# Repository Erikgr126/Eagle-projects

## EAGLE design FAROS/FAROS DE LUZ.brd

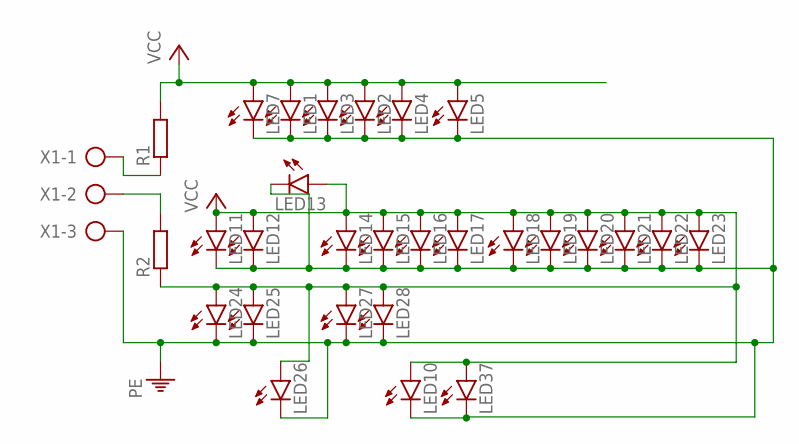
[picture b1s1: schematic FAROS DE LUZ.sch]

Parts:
LED1, LED2, LED3, LED4, LED5, LED7: LED10MM
LED10, LED11, LED12, LED13, LED14, LED15, LED16, LED17, LED18, LED19, LED20, LED21, LED22, LED23, LED24, LED25, LED26, LED27, LED28, LED37: LED5MM
R1, R2: R-EU_0204/7; 0204/7
X1: AK500/3-H

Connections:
unnamed: R1.1, X1.1
unnamed: R2.2, X1.2
PE: LED1.K (C), LED2.K (C), LED3.K (C), LED4.K (C), LED5.K (C), LED7.K (C), LED10.K (C), LED11.K (C), LED12.K (C), LED13.K (C), LED14.K (C), LED15.K (C), LED16.K (C), LED17.K (C), LED18.K (C), LED19.K (C), LED20.K (C), LED21.K (C), LED22.K (C), LED23.K (C), LED24.K (C), LED25.K (C), LED26.K (C), LED27.K (C), LED28.K (C), LED37.K (C), X1.3
VCC: LED1.A, LED2.A, LED3.A, LED4.A, LED5.A, LED7.A, LED10.A, LED11.A, LED12.A, LED13.A, LED14.A, LED15.A, LED16.A, LED17.A, LED18.A, LED19.A, LED20.A, LED21.A, LED22.A, LED23.A, LED24.A, LED25.A, LED26.A, LED27.A, LED28.A, LED37.A, R1.2, R2.1

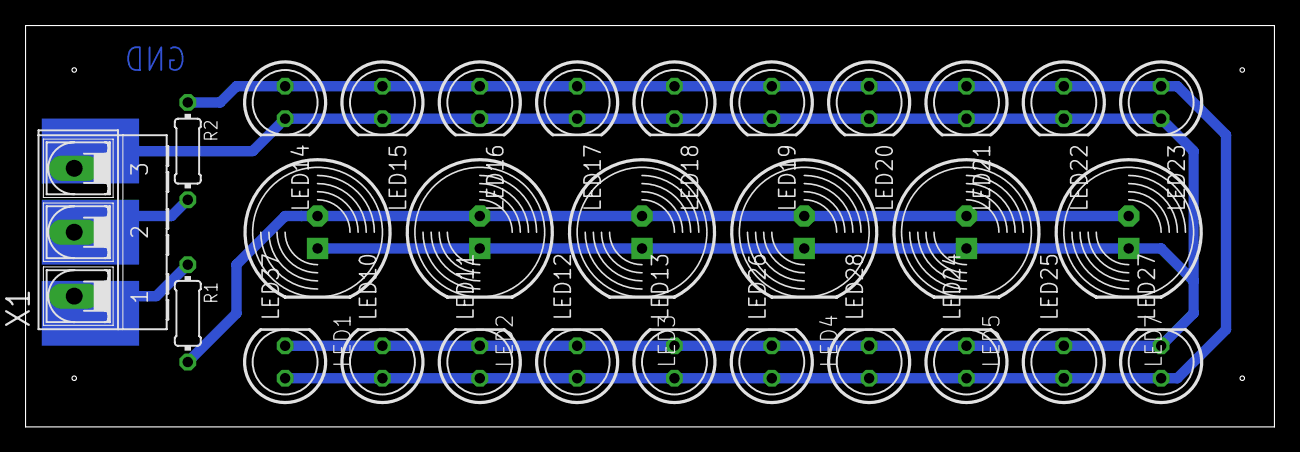
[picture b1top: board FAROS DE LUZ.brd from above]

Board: 2 copper layers, 97.8 x 31.4 mm, 29 parts (0 on the bottom side), 4 nets.

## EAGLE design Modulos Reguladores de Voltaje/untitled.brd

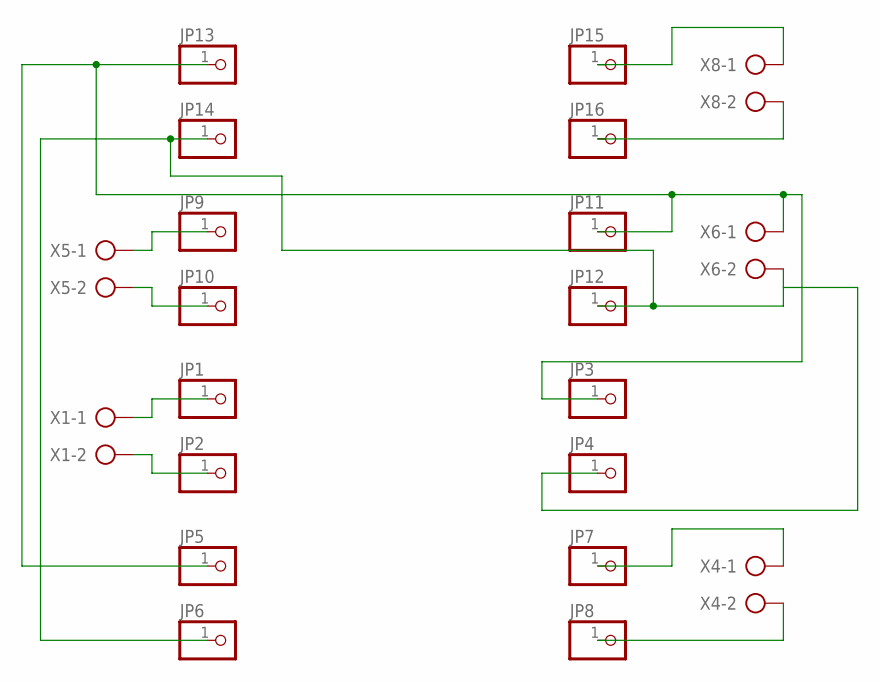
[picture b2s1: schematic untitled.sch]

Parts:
JP1, JP2, JP3, JP4, JP5, JP6, JP7, JP8, JP9, JP10, JP11, JP12, JP13, JP14, JP15, JP16: PINHD-1X1; 1X01
X1, X4, X5, X6, X8: AK500/2-H

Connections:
unnamed: JP1.1, X1.1
unnamed: JP2.1, X1.2
unnamed: JP3.1, JP5.1, JP11.1, JP13.1, X6.1
unnamed: JP4.1, JP6.1, JP12.1, JP14.1, X6.2
unnamed: JP7.1, X4.1
unnamed: JP8.1, X4.2
unnamed: JP9.1, X5.1
unnamed: JP10.1, X5.2
unnamed: JP15.1, X8.1
unnamed: JP16.1, X8.2

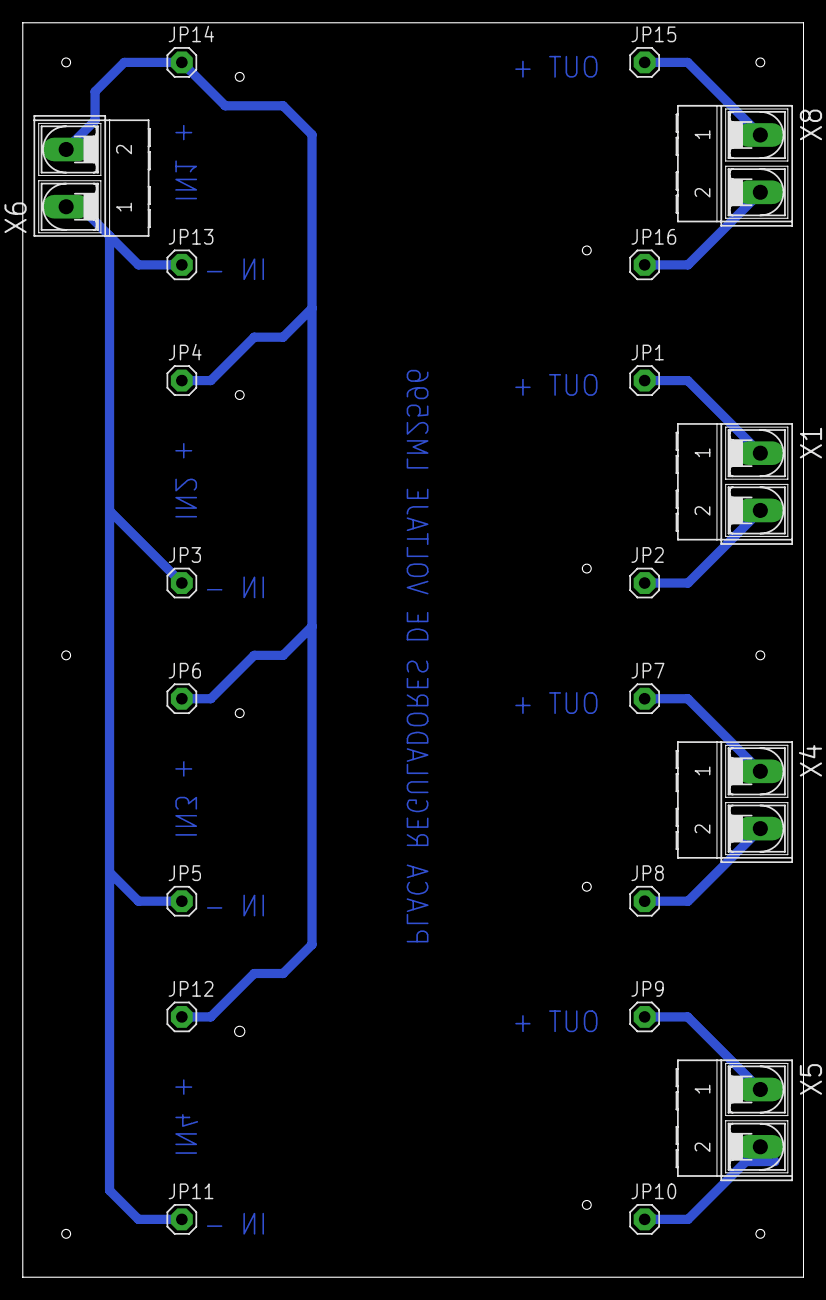
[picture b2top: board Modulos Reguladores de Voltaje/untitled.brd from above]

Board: 2 copper layers, 68.6 x 110.2 mm, 21 parts (0 on the bottom side), 10 nets.

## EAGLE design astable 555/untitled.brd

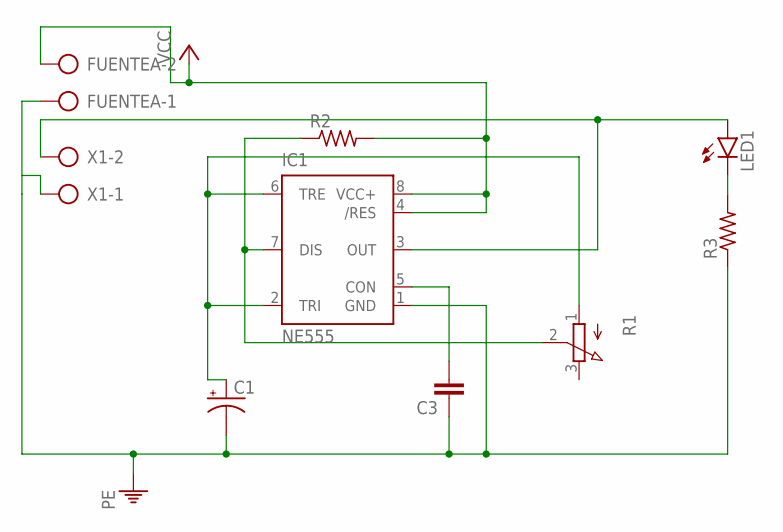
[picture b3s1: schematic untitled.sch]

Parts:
C1: CPOL-USE1.8-4; E1,8-4
C3: C2,5-3; C2.5-3
FUENTEA: AK500/2-H
IC1: NE555; DIL-08
LED1: LED5MM
R1: 3RP/1610N
R2, R3: R-US_0204/7; 0204/7
X1: AK500/2-H

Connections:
unnamed: IC1.3 (OUT), LED1.A, X1.2
unnamed: C1.+, IC1.2 (TRI), IC1.6 (TRE), R1.1 (A)
unnamed: LED1.K (C), R3.2
unnamed: C3.2, IC1.5 (CON)
unnamed: IC1.7 (DIS), R1.2 (S), R2.1
PE: C1.-, C3.1, FUENTEA.1, IC1.1 (GND), R3.1, X1.1
VCC: FUENTEA.2, IC1.4 (/RES), IC1.8 (VCC+), R2.2

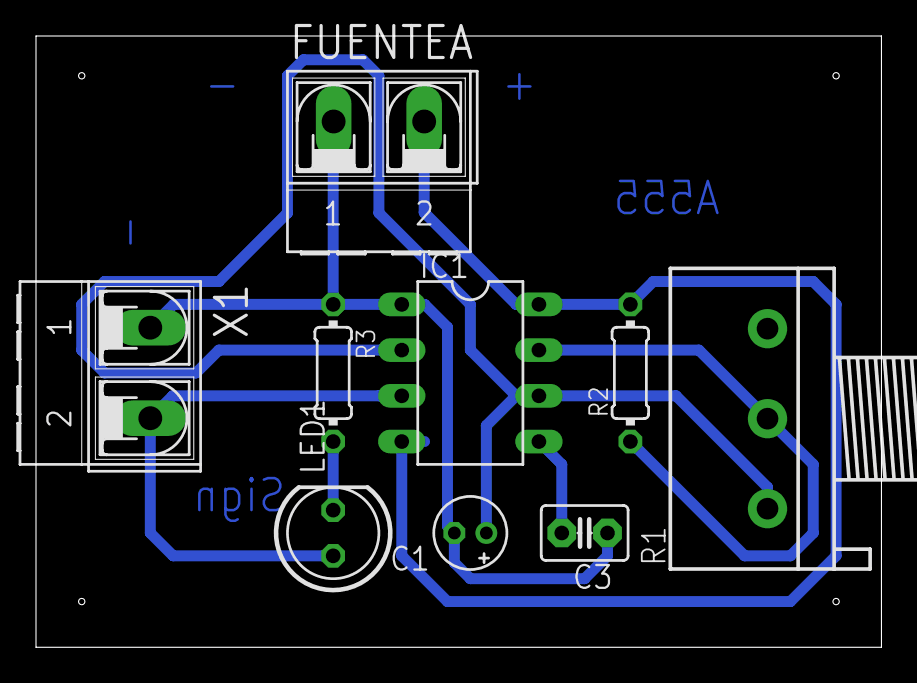
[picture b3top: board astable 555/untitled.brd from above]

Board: 2 copper layers, 47.0 x 34.0 mm, 9 parts (0 on the bottom side), 7 nets.

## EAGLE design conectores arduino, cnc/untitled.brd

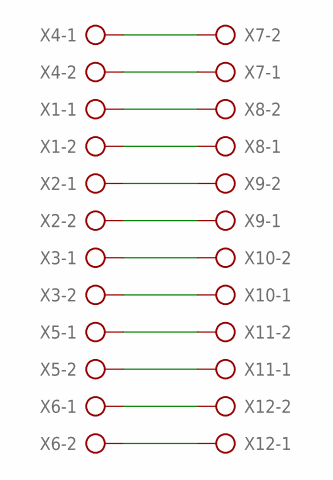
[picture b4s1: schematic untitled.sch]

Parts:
X1, X2, X3, X4, X5, X6, X7, X8, X9, X10, X11, X12: AK500/2-H

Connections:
unnamed: X4.1, X7.2
unnamed: X4.2, X7.1
unnamed: X1.1, X8.2
unnamed: X1.2, X8.1
unnamed: X2.1, X9.2
unnamed: X2.2, X9.1
unnamed: X3.1, X10.2
unnamed: X3.2, X10.1
unnamed: X5.1, X11.2
unnamed: X5.2, X11.1
unnamed: X6.1, X12.2
unnamed: X6.2, X12.1

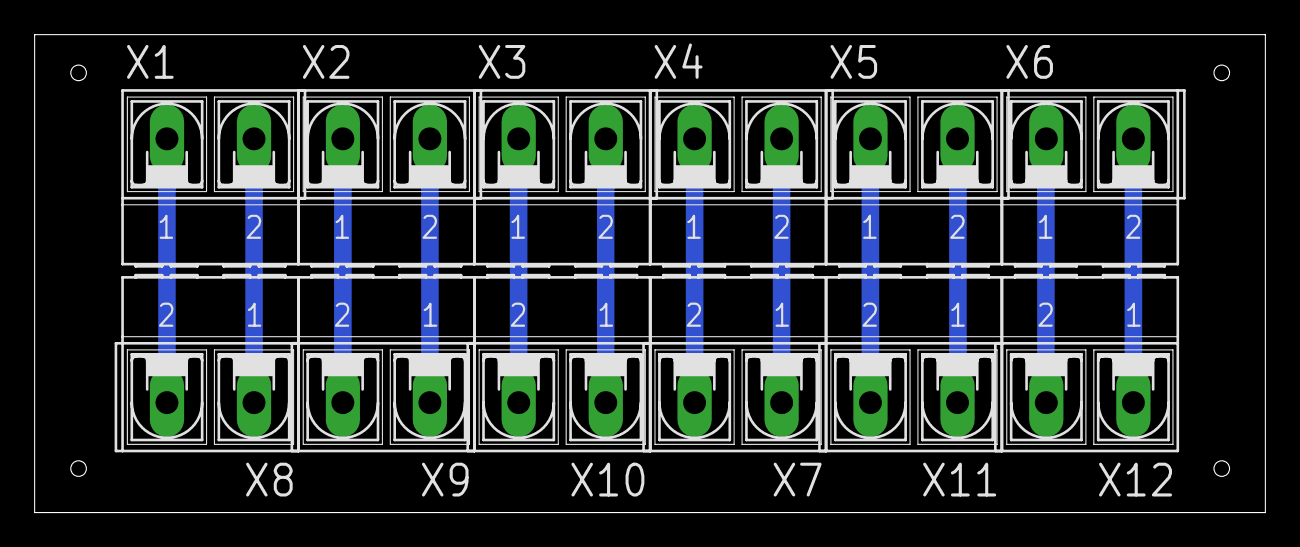
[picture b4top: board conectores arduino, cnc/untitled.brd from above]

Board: 2 copper layers, 71.1 x 27.6 mm, 12 parts (0 on the bottom side), 12 nets.

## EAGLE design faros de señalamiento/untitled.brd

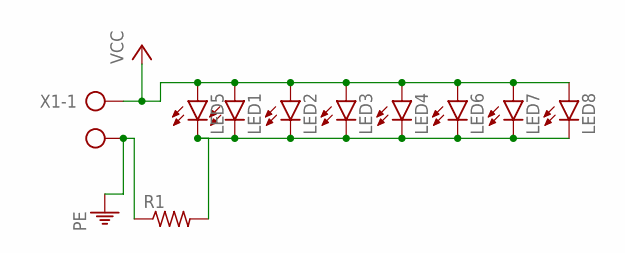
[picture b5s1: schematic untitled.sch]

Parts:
LED1, LED2, LED3, LED4, LED5, LED6, LED7, LED8: LED5MM
R1: R-US_0204/7; 0204/7
X1: AK500/2-H

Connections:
unnamed: LED1.K (C), LED2.K (C), LED3.K (C), LED4.K (C), LED5.K (C), LED6.K (C), LED7.K (C), LED8.K (C), R1.2
PE: R1.1, X1.2
VCC: LED1.A, LED2.A, LED3.A, LED4.A, LED5.A, LED6.A, LED7.A, LED8.A, X1.1

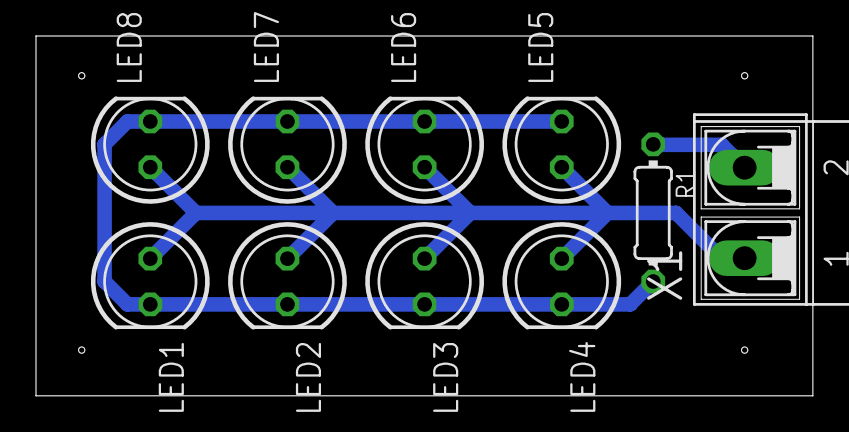
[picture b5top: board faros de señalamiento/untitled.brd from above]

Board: 2 copper layers, 43.2 x 20.0 mm, 10 parts (0 on the bottom side), 3 nets.
